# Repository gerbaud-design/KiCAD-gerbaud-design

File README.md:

# KiCAD-gerbaud-design
all the KiCAD files for gerbaud design products and libraries

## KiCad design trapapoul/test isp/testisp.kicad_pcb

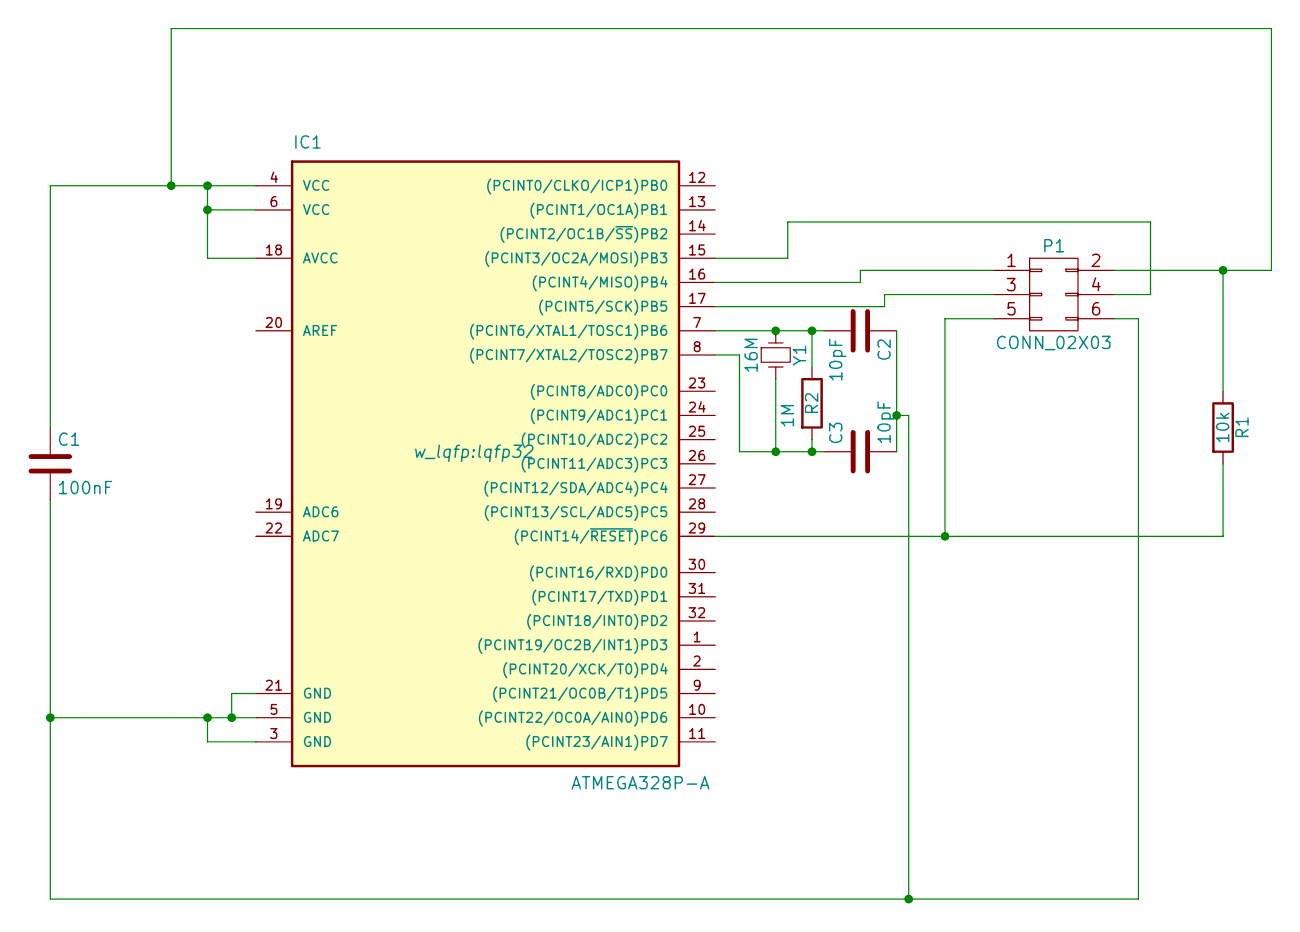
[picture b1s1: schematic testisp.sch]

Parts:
C1: 100nF; C_1206_HandSoldering
C2, C3: 10pF; C_1206_HandSoldering
IC1: ATMEGA328P-A; lqfp32
P1: CONN_02X03; Pin_Header_Straight_2x03_Pitch2.54mm
R1: 10k; R_1206_HandSoldering
R2: 1M; R_1206_HandSoldering
Y1: 16M; Crystal_HC49-SD_SMD

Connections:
unnamed: C1.1, IC1.4 (VCC), IC1.6 (VCC), IC1.18 (AVCC), P1.2, R1.1
unnamed: C1.2, C2.1, C3.2, IC1.3 (GND), IC1.5 (GND), IC1.21 (GND), P1.6
unnamed: C2.2, IC1.7 ((PCINT6/XTAL1/TOSC1)PB6), R2.1, Y1.1
unnamed: C3.1, IC1.8 ((PCINT7/XTAL2/TOSC2)PB7), R2.2, Y1.2
unnamed: IC1.15 ((PCINT3/OC2A/MOSI)PB3), P1.4
unnamed: IC1.16 ((PCINT4/MISO)PB4), P1.1
unnamed: IC1.17 ((PCINT5/SCK)PB5), P1.3
unnamed: IC1.29 ((PCINT14/~RESET~)PC6), P1.5, R1.2

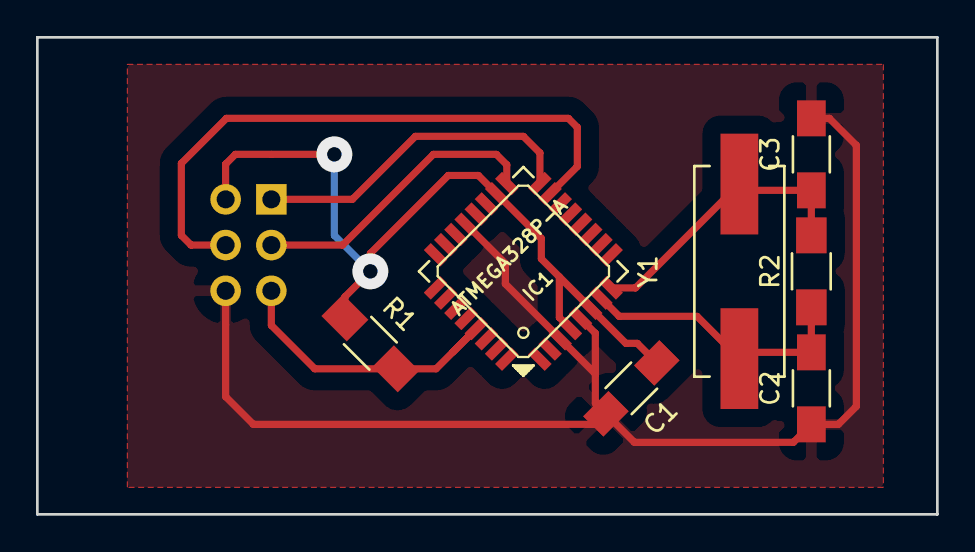
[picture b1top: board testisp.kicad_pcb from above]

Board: 2 copper layers, 50.0 x 26.5 mm, 8 parts (1 on the bottom side), 8 nets.

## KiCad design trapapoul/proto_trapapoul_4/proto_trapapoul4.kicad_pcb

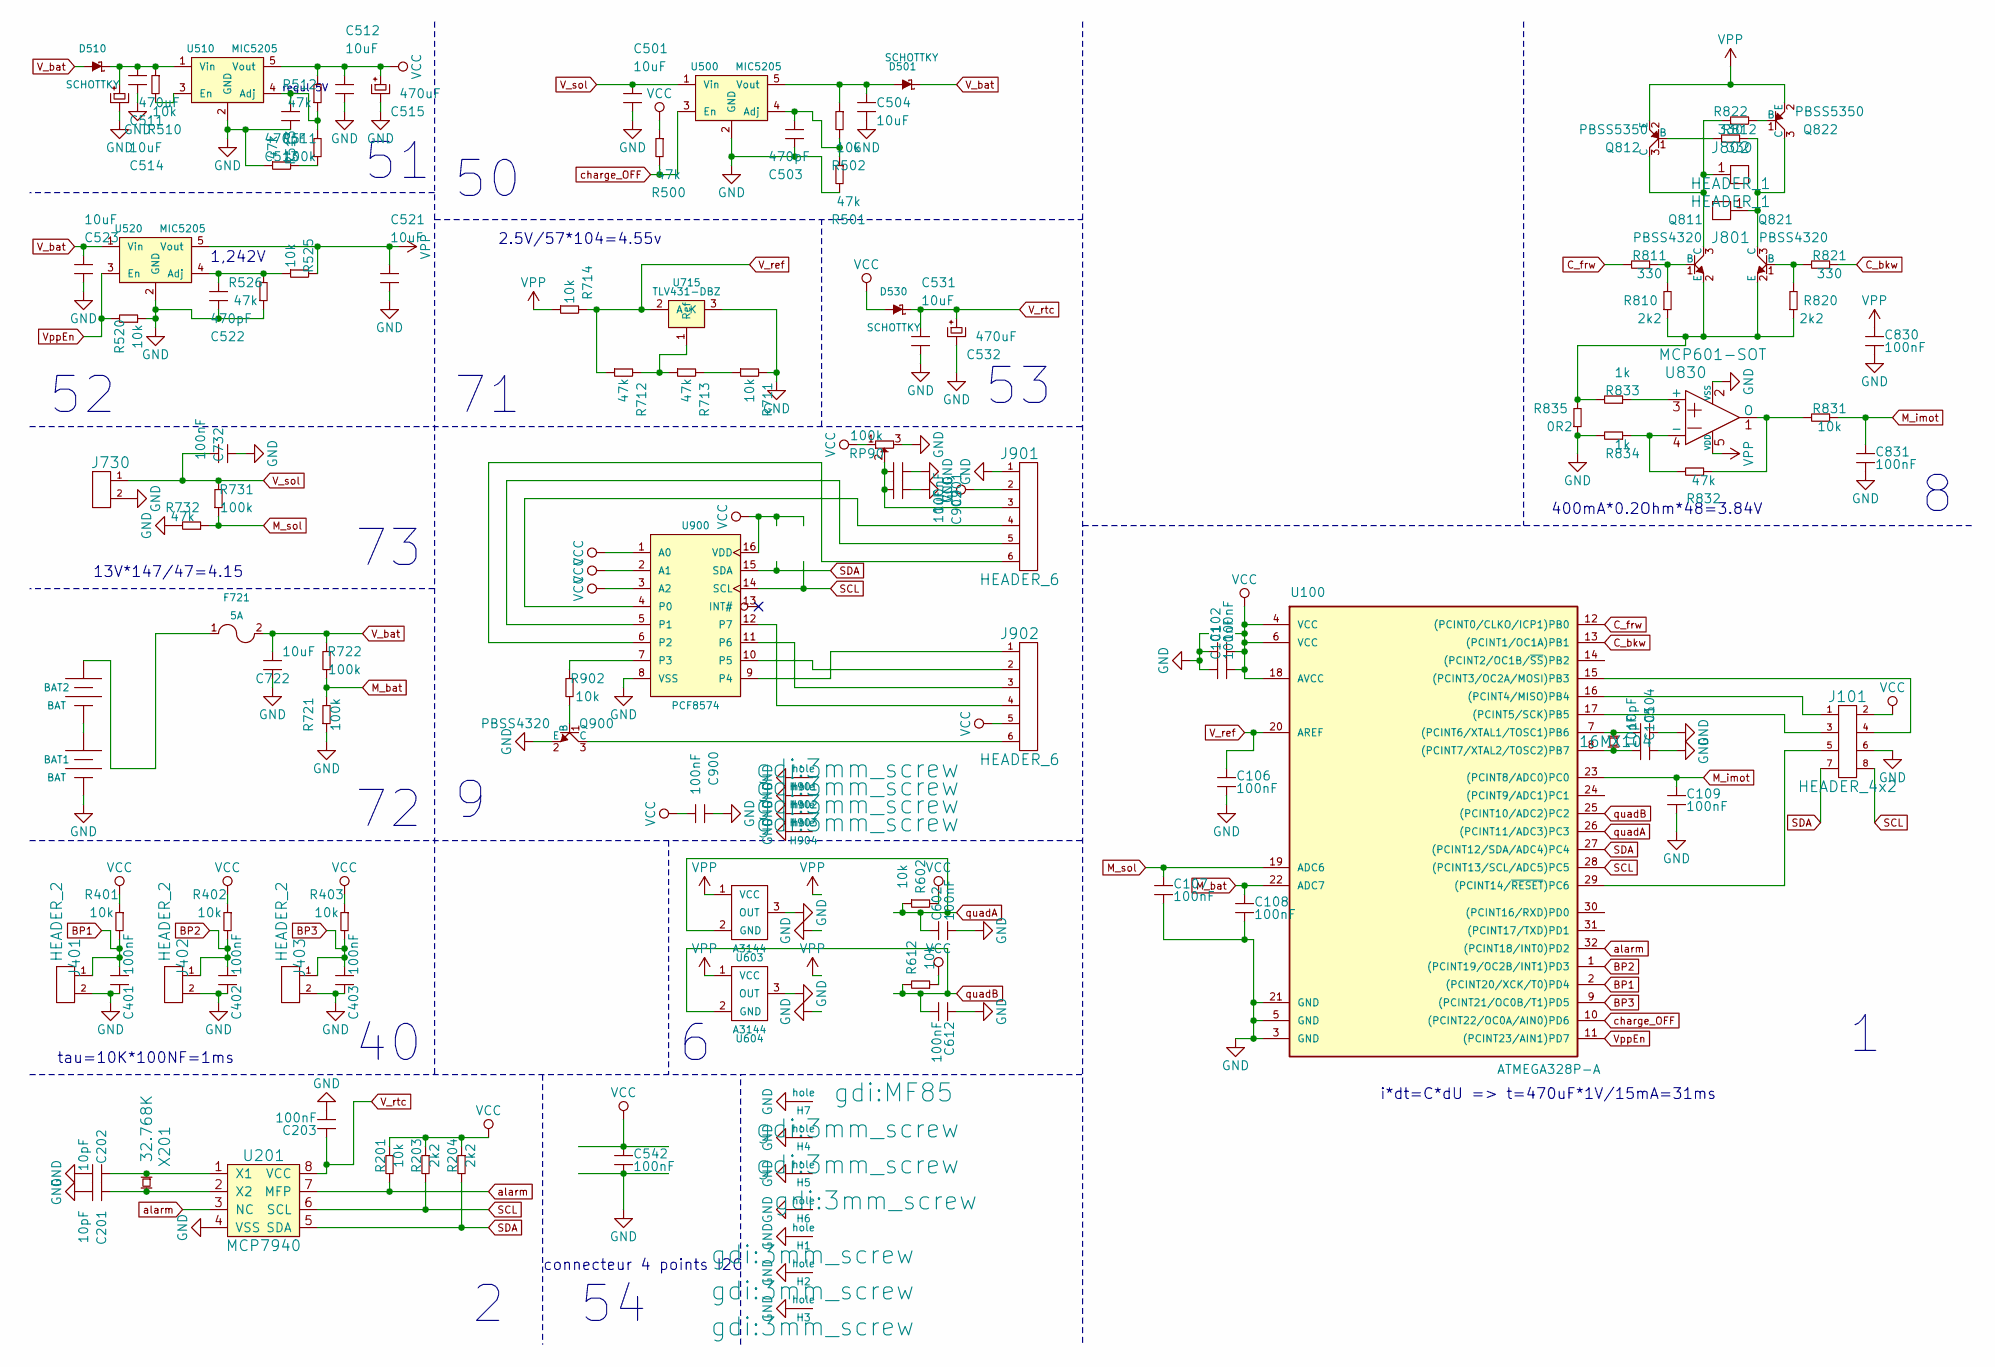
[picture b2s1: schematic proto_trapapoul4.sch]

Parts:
BAT1, BAT2: BAT; HFC1330
C101, C102, C106, C107, C108, C109, C203, C401, C402, C403, C542, C602, C612, C732, C830, C831, C900, C901: 100nF; C_1206
C104, C105, C201, C202: 10pF; C_1206
C501, C504, C512, C514, C521, C523, C531, C722, C902: 10uF; C_1206
C503, C513, C522: 470pF; C_1206
C511, C515, C532: 470uF; C_Radial_D6.3_L11.2_P2.5
D501, D510, D530: SCHOTTKY; SOD-123
F721: 5A; Fuse_SMD1206_Reflow
H1, H2, H3, H4, H5, H6, H901, H902, H903, H904: hole; 3mm_screw
H7: hole; MF85
J101: HEADER_4x2; Pin_Header_Straight_2x04_Pitch2.54mm
J401, J402, J403, J730: HEADER_2; Pin_Header_Straight_1x02
J801, J802: HEADER_1; Pin_Header_Straight_1x01
J901, J902: HEADER_6; Pin_Header_Straight_1x06
Q811, Q821, Q900: PBSS4320; SOT-23
Q812, Q822: PBSS5350; SOT-23
R201, R401, R402, R403, R502, R510, R520, R525, R602, R612, R711, R714, R831, R902: 10k; R_1206
R203, R204, R810, R820: 2k2; R_1206
R500, R501, R512, R513, R526, R712, R713, R732, R832: 47k; R_1206
R511, R721, R722, R731: 100k; R_1206
R811, R812, R821, R822: 330; R_1206
R833, R834: 1k; R_1206
R835: 0R2; R_1206
RP90: 100k; Potentiometer_Triwood_RM-065
U100: ATMEGA328P-A; lqfp32
U201: MCP7940; SOIC-8-N
U500, U510, U520: MIC5205; SOT-23-5
U603, U604: A3144; SOT-23
U715: TLV431-DBZ; SOT-23
U830: MCP601-SOT; SOT-23-5
U900: PCF8574; SO-16-W
X104: 16M; Crystal_HC49-SD_SMD
X201: 32.768K; Crystal_Round_Vertical_3mm_BigPad

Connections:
BP1: C401.1, J401.1, R401.2, U100.2 ((PCINT20/XCK/T0)PD4)
BP2: C402.1, J402.1, R402.2, U100.1 ((PCINT19/OC2B/INT1)PD3)
BP3: C403.1, J403.1, R403.2, U100.9 ((PCINT21/OC0B/T1)PD5)
C_bkw: R821.1, U100.13 ((PCINT1/OC1A)PB1)
C_frw: R811.2, U100.12 ((PCINT0/CLKO/ICP1)PB0)
GND: BAT1.2 (-), C101.1, C102.1, C104.1, C105.1, C106.2, C107.2, C108.2, C109.2, C201.2, C202.2, C203.2, C401.2, C402.2, C403.2, C501.2, C503.2, C504.2, C511.2, C512.2, C513.2, C514.2, C515.2, C521.2, C522.2, C523.2, C531.2, C532.2, C542.2, C602.2, C612.1, C722.2, C732.1, C830.2, C831.2, C900.2, C901.1, C902.1, H1.1, H2.1, H3.1, H4.1, H5.1, H6.1, H7.1, H901.1, H902.1, H903.1, H904.1, J101.6, J401.2, J402.2, J403.2, J730.2, J901.1, Q900.2 (E), R501.2, R513.1, R520.1, R526.1, R711.2, R721.1, R732.2, R834.2, R835.1, RP90.3, U100.3 (GND), U100.5 (GND), U100.21 (GND), U201.4 (VSS), U500.2 (GND), U510.2 (GND), U520.2 (GND), U603.3 (OUT), U604.3 (OUT), U715.3 (K), U830.2 (VSS), U900.8 (VSS)
M_bat: C108.1, R721.2, R722.2, U100.22 (ADC7)
M_imot: C109.1, C831.1, R831.1, U100.23 ((PCINT8/ADC0)PC0)
M_sol: C107.1, R731.1, R732.1, U100.19 (ADC6)
unnamed: BAT1.1 (+), BAT2.2 (-)
unnamed: BAT2.1 (+), F721.1
unnamed: C104.2, U100.7 ((PCINT6/XTAL1/TOSC1)PB6), X104.1
unnamed: C105.2, U100.8 ((PCINT7/XTAL2/TOSC2)PB7), X104.2
unnamed: C201.1, U201.2 (X2), X201.2
unnamed: C202.1, U201.1 (X1), X201.1
unnamed: C503.1, R501.1, R502.2, U500.4 (Adj)
unnamed: C504.1, D501.2 (A), R502.1, U500.5 (Vout)
unnamed: C511.1, C514.1, D510.1 (K), R510.1, U510.1 (Vin)
unnamed: C513.1, R511.2, R512.1, U510.4 (Adj)
unnamed: C522.1, R525.1, R526.2, U520.4 (Adj)
unnamed: C901.2, C902.2, J901.3, RP90.2
unnamed: J101.1, U100.16 ((PCINT4/MISO)PB4)
unnamed: J101.3, U100.17 ((PCINT5/SCK)PB5)
unnamed: J101.4, U100.15 ((PCINT3/OC2A/MOSI)PB3)
unnamed: J101.5, U100.29 ((PCINT14/~RESET~)PC6)
unnamed: J801.1, Q821.3 (C), Q822.3 (C), R812.1
unnamed: J802.1, Q811.3 (C), Q812.3 (C), R822.1
unnamed: J901.4, U900.4 (P0)
unnamed: J901.5, U900.5 (P1)
unnamed: J901.6, U900.6 (P2)
unnamed: J902.1, U900.9 (P4)
unnamed: J902.2, U900.10 (P5)
unnamed: J902.3, U900.11 (P6)
unnamed: J902.4, U900.12 (P7)
unnamed: J902.6, Q900.3 (C)
unnamed: Q811.1 (B), R810.2, R811.1
unnamed: Q811.2 (E), Q821.2 (E), R810.1, R820.1, R833.2, R835.2
unnamed: Q812.1 (B), R812.2
unnamed: Q821.1 (B), R820.2, R821.2
unnamed: Q822.1 (B), R822.2
unnamed: Q900.1 (B), R902.2
unnamed: R510.2, U510.3 (En)
unnamed: R511.1, R513.2
unnamed: R711.1, R713.2
unnamed: R712.2, R713.1, U715.1 (Ref)
unnamed: R831.2, R832.1, U830.1 (O)
unnamed: R832.2, R834.1, U830.4 (-)
unnamed: R833.1, U830.3 (+)
unnamed: R902.1, U900.7 (P3)
SCL: J101.8, R203.2, U100.28 ((PCINT13/SCL/ADC5)PC5), U201.6 (SCL), U900.14 (SCL)
SDA: J101.7, R204.2, U100.27 ((PCINT12/SDA/ADC4)PC4), U201.5 (SDA), U900.15 (SDA)
VCC: C101.2, C102.2, C512.1, C515.1, C542.1, C900.1, D530.2 (A), J101.2, J901.2, J902.5, R201.1, R203.1, R204.1, R401.1, R402.1, R403.1, R500.1, R512.2, R602.2, R612.1, RP90.1, U100.4 (VCC), U100.6 (VCC), U100.18 (AVCC), U510.5 (Vout), U900.1 (A0), U900.2 (A1), U900.3 (A2), U900.16 (VDD)
VPP: C521.1, C830.1, Q812.2 (E), Q822.2 (E), R525.2, R714.1, U520.5 (Vout), U603.1 (VCC), U604.1 (VCC), U830.5 (VDD)
V_bat: C523.1, C722.1, D501.1 (K), D510.2 (A), F721.2, R722.1, U520.1 (Vin)
V_ref: C106.1, R712.1, R714.2, U100.20 (AREF), U715.2 (A)
V_rtc: C203.1, C531.1, C532.1, D530.1 (K), U201.8 (VCC)
V_sol: C501.1, C732.2, J730.1, R731.2, U500.1 (Vin)
VppEn: R520.2, U100.11 ((PCINT23/AIN1)PD7), U520.3 (En)
alarm: R201.2, U100.32 ((PCINT18/INT0)PD2), U201.3 (NC), U201.7 (MFP)
charge_OFF: R500.2, U100.10 ((PCINT22/OC0A/AIN0)PD6), U500.3 (En)
quadA: C602.1, R602.1, U100.26 ((PCINT11/ADC3)PC3), U603.2 (GND)
quadB: C612.2, R612.2, U100.25 ((PCINT10/ADC2)PC2), U604.2 (GND)

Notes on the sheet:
regul 5V
connecteur 4 points I2C
1,242V
2.5V/57*104=4.55v
tau=10K*100NF=1ms
13V*147/47=4.15
400mA*0.2Ohm*48=3.84V
i*dt=C*dU => t=470uF*1V/15mA=31ms

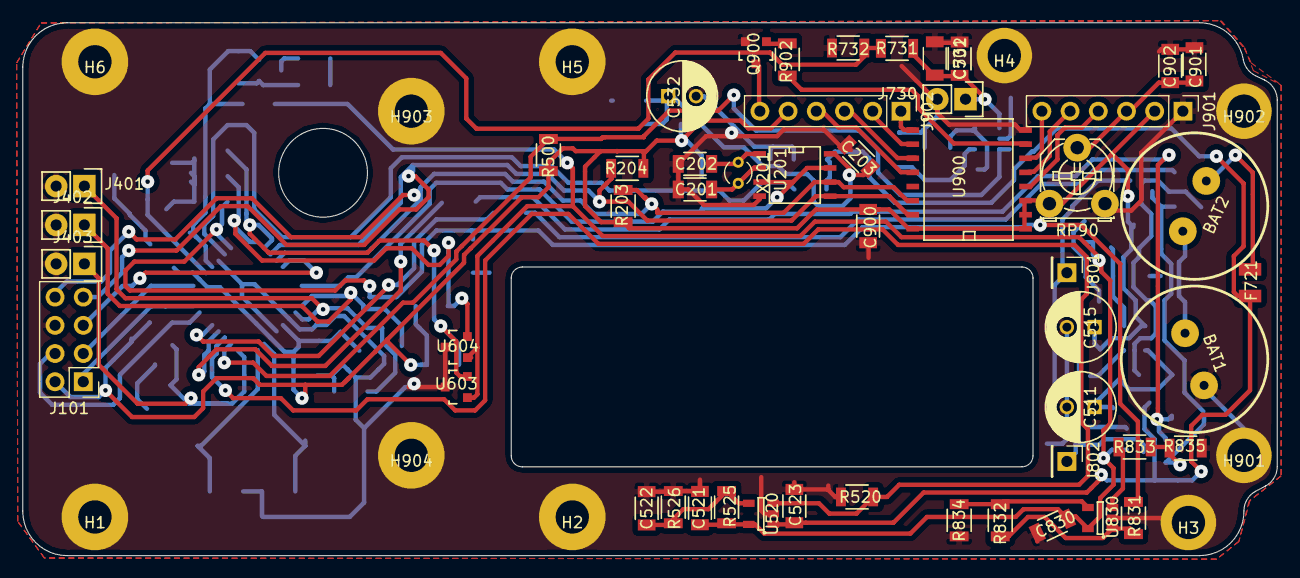
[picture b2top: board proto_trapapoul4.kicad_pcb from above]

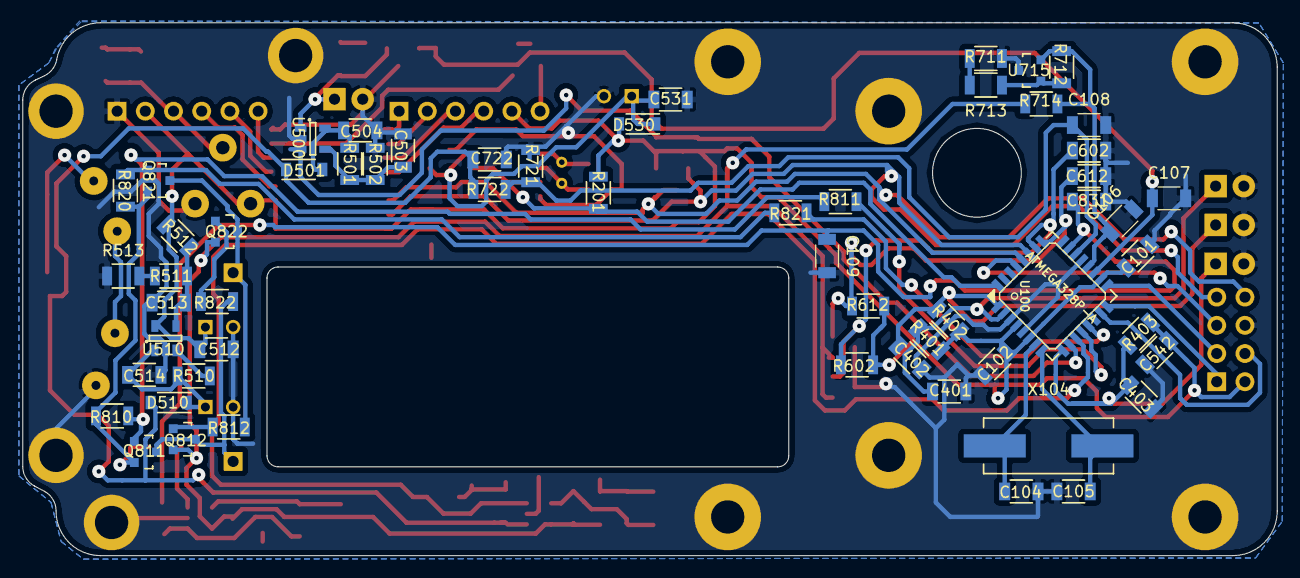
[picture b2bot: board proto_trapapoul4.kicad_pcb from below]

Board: 2 copper layers, 113.0 x 48.0 mm, 118 parts (58 on the bottom side), 62 nets.

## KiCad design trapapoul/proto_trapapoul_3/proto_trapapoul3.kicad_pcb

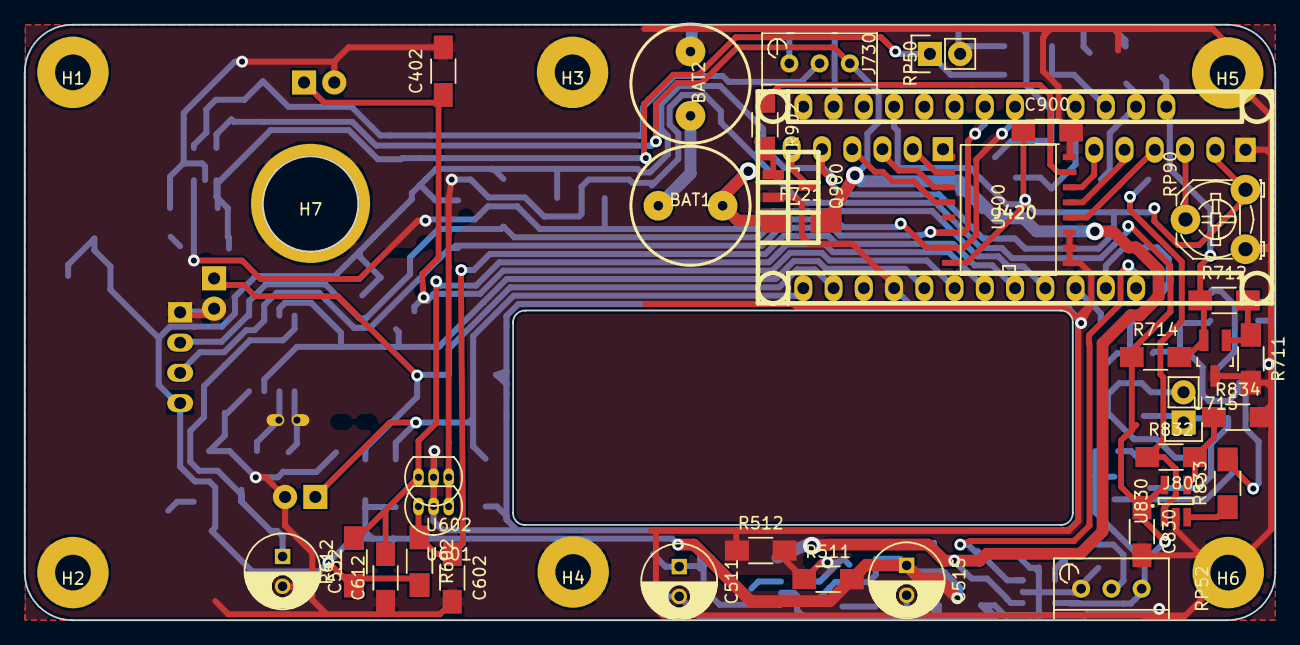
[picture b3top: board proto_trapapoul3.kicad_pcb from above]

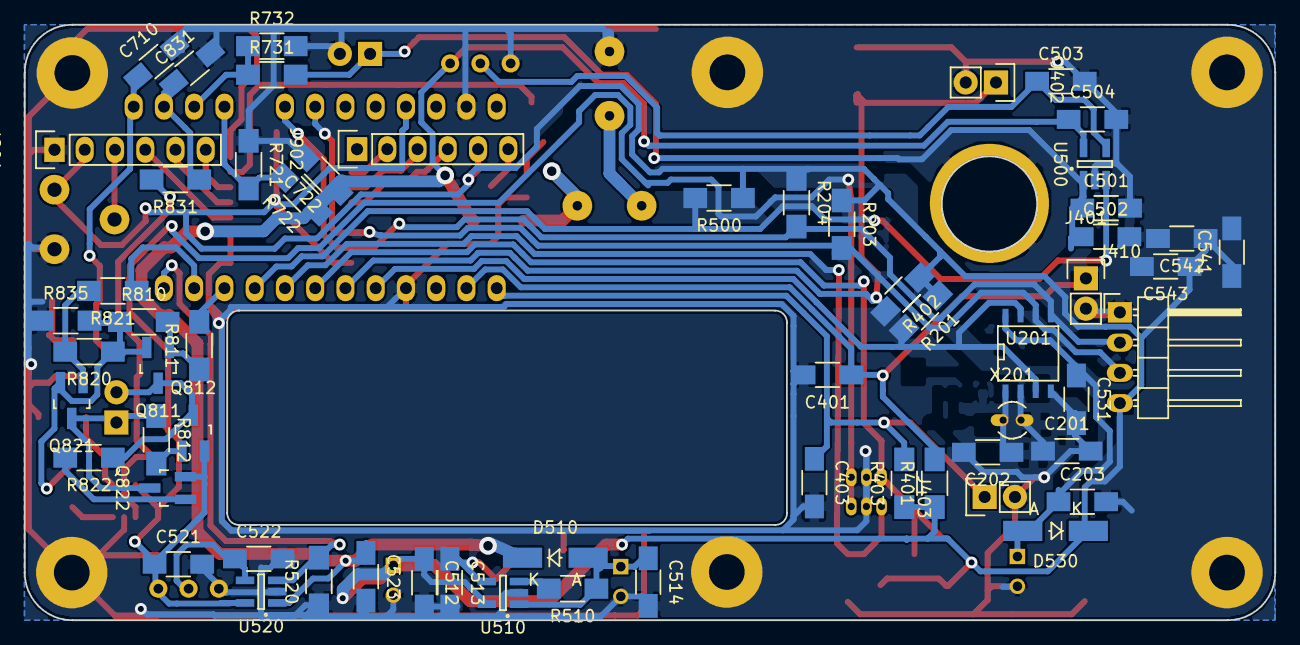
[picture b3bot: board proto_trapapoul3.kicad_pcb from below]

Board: 2 copper layers, 105.0 x 50.0 mm, 101 parts (60 on the bottom side), 53 nets.

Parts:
BAT1, BAT2: BAT; HFC1025
C201, C202: 10p; C_1206_HandSoldering
C203, C401, C402, C403, C502, C541, C710: 10n; C_1206_HandSoldering
C501, C504, C512, C514, C521, C523, C531, C543, C722: 10uF; C_1206_HandSoldering
C503, C513, C522: 470p; C_1206_HandSoldering
C511, C515, C532: 470uF; C_Radial_D6.3_L11.2_P2.5
C542, C602, C612, C900: 100nF; C_1206_HandSoldering
C830, C831: 100n; C_1206_HandSoldering
D510, D530: SCHOTTKY; MiniMELF_Handsoldering
F721: 5A; Fuse_SMD1206_HandSoldering
H1, H2, H3, H4, H5, H6: hole; 3mm_screw
H7: hole; MF85
J401, J402, J403, J730, J800: HEADER_2; Pin_Header_Straight_1x02
J410: HEADER_4; Pin_Header_Angled_1x04
J420: Arduino_Nano_Header; arduino_nano_header
J901, J902: HEADER_6; Pin_Header_Straight_1x06
Q811, Q821, Q900: PBSS4320; SOT-23_Handsoldering
Q812, Q822: PBSS5350; SOT-23_Handsoldering
R201, R401, R402, R403, R500, R510, R511, R520, R711, R714, R722, R731, R832: 10k; R_1206_HandSoldering
R203, R204, R732: 2.2k; R_1206_HandSoldering
R512, R810, R820: 3k3; R_1206_HandSoldering
R602, R612: 4k7; R_1206_HandSoldering
R712, R721, R902: 4.7k; R_1206_HandSoldering
R811, R812, R821, R822: 330; R_1206_HandSoldering
R831, R833, R834: 1k; R_1206_HandSoldering
R835: 0R2; R_1206_HandSoldering
RP50, RP52: 10k; Potentiometer_Bourns_3296W_3-8Zoll_Inline_ScrewUp
RP90: 10k; Potentiometer_Triwood_RM-065
U201: MCP7940; SOIC-8-N
U500, U510, U520: MIC5205; SOT-23-5_Handsoldering
U601, U602: A3144; TO-92_Inline_Narrow_Oval
U715: TLV431-DBZ; SOT-23_Handsoldering
U830: MCP601-SOT; SOT-23-5_Handsoldering
U900: PCF8574; SO-16-W
X201: 32.768K; Crystal_Round_Vertical_3mm_BigPad

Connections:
BP1: C401.1, J401.1, J420.2, R401.2
BP2: C402.1, J402.1, J420.6, R402.2
BP3: C403.1, J403.1, J420.1, R403.2
C_bkw: J420.11, R821.1
C_frw: J420.10, R811.2
GND: BAT2.2, C201.2, C202.2, C203.2, C401.2, C402.2, C403.2, C501.2, C502.2, C503.2, C504.2, C511.2, C512.2, C513.2, C514.2, C515.2, C521.2, C522.2, C523.2, C531.2, C532.2, C541.2, C542.2, C543.2, C602.2, C612.1, C710.2, C722.2, C830.2, C831.2, C900.2, H1.1, H2.1, H3.1, H4.1, H5.1, H6.1, H7.1, J401.2, J402.2, J403.2, J410.1, J420.4, J420.29, J730.2, J901.1, Q900.2, R512.1, R520.1, R711.2, R721.1, R732.2, R834.2, R835.1, RP50.1, RP52.1, RP90.1, U201.4, U500.2, U510.2, U520.2, U601.2, U602.2, U715.3, U830.2, U900.1, U900.2, U900.3, U900.8
M_bat: J420.21, R721.2, R722.2
M_imot: C831.1, J420.19, R831.1
M_sol: J420.20, R731.1, R732.1
unnamed: BAT1.1, F721.1
unnamed: BAT1.2, BAT2.1
unnamed: C201.1, U201.2, X201.2
unnamed: C202.1, U201.1, X201.1
unnamed: C503.1, RP50.2, U500.4
unnamed: C511.1, C514.1, D510.2, R510.1, U510.1
unnamed: C513.1, R511.1, R512.2, U510.4
unnamed: C522.1, RP52.2, U520.4
unnamed: J901.3, RP90.2
unnamed: J901.4, U900.4
unnamed: J901.5, U900.5
unnamed: J901.6, U900.6
unnamed: J902.1, U900.9
unnamed: J902.2, U900.10
unnamed: J902.3, U900.11
unnamed: J902.4, U900.12
unnamed: J902.6, Q900.3
unnamed: Q811.1, R810.2, R811.1
unnamed: Q811.2, Q821.2, R810.1, R820.1, R833.2, R835.2
unnamed: Q812.1, R812.2
unnamed: Q821.1, R820.2, R821.2
unnamed: Q822.1, R822.2
unnamed: Q900.1, R902.2
unnamed: R510.2, U510.3
unnamed: R711.1, R712.2, U715.1
unnamed: R831.2, R832.1, U830.1
unnamed: R832.2, R834.1, U830.4
unnamed: R833.1, U830.3
unnamed: R902.1, U900.7
SCL: J410.3, J420.24, R203.2, U201.6, U900.14
SDA: J410.2, J420.23, R204.2, U201.5, U900.15
VCC: C512.1, C515.1, C541.1, C542.1, C543.1, C900.1, D530.1, J410.4, J420.27, J901.2, J902.5, R201.1, R203.1, R204.1, R401.1, R402.1, R403.1, R500.1, R511.2, R602.2, R612.1, RP90.3, U510.5, U900.16
VPP: C521.1, C830.1, Q812.2, Q822.2, R714.1, RP52.3, U520.5, U601.1, U602.1, U830.5
V_bat: C504.1, C523.1, C722.1, D510.1, F721.2, R722.1, RP50.3, U500.5, U520.1
V_ref: C710.1, J420.18, R712.1, R714.2, U715.2
V_rtc: C203.1, C531.1, C532.1, D530.2, U201.8
V_sol: C501.1, C502.1, J730.1, R731.2, U500.1
VppEn: J420.12, R520.2, U520.3
alarm: J420.5, R201.2, U201.3, U201.7
charge_OFF: J420.9, R500.2, U500.3
mot_A: J800.1, Q821.3, Q822.3, R812.1
mot_B: J800.2, Q811.3, Q812.3, R822.1
quadA: C602.1, J420.8, R602.1, U601.3
quadB: C612.2, J420.7, R612.2, U602.3

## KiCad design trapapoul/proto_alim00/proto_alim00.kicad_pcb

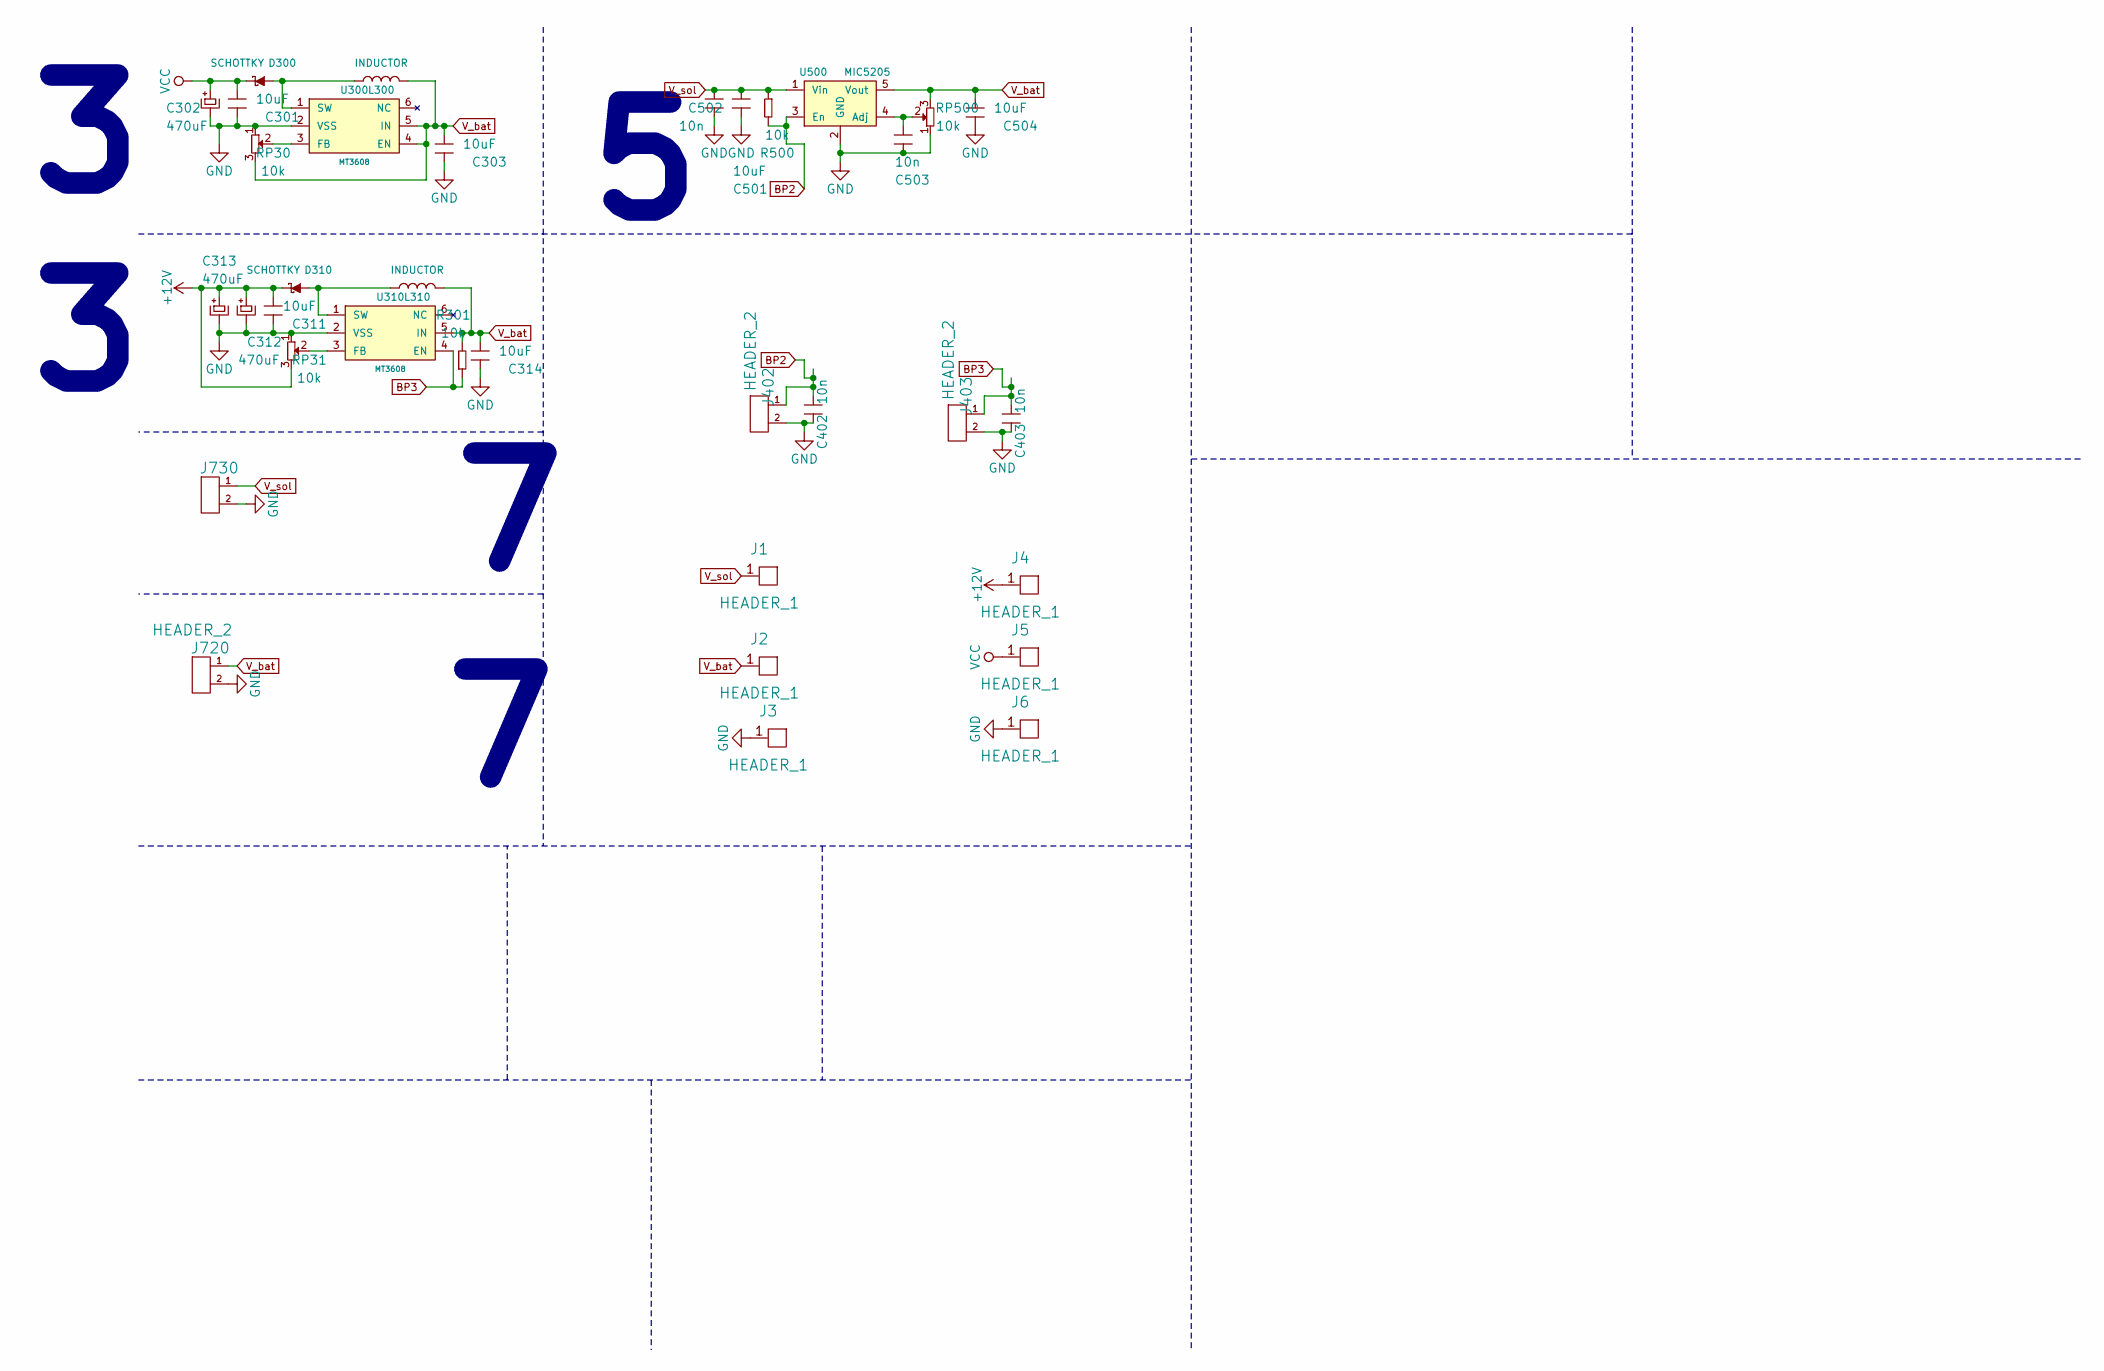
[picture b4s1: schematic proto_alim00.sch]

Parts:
C301, C303, C311, C314, C501, C504: 10uF; C_1206_HandSoldering
C302, C312, C313: 470uF; C_Radial_D8_L11.5_P3.5
C402, C403, C502, C503: 10n; C_1206_HandSoldering
D300, D310: SCHOTTKY; MiniMELF_Handsoldering
J1, J2, J3, J4, J5, J6: HEADER_1; Pin_Header_Straight_1x01
J402, J403, J720, J730: HEADER_2; Pin_Header_Straight_1x02
L300, L310: INDUCTOR; R_1206_HandSoldering
R301, R500: 10k; R_1206_HandSoldering
RP30, RP31, RP500: 10k; Potentiometer_Triwood_RM-065
U300, U310: MT3608; SOT-23-6_Handsoldering
U500: MIC5205; SOT-23-5_Handsoldering

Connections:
+12V: C311.1, C312.1, C313.1, D310.2 (K), J4.1, RP31.3
BP2: C402.1, J402.1, R500.2, U500.3 (En)
BP3: C403.1, J403.1, R301.1, U310.4 (EN)
GND: C301.2, C302.2, C303.2, C311.2, C312.2, C313.2, C314.2, C402.2, C403.2, C501.2, C502.2, C503.2, C504.2, J3.1, J6.1, J402.2, J403.2, J720.2, J730.2, RP30.1, RP31.1, RP500.1, U300.2 (VSS), U310.2 (VSS), U500.2 (GND)
unnamed: C503.1, RP500.2, U500.4 (Adj)
unnamed: D300.1 (A), L300.1, U300.1 (SW)
unnamed: D310.1 (A), L310.1, U310.1 (SW)
unnamed: RP30.2, U300.3 (FB)
unnamed: RP31.2, U310.3 (FB)
VCC: C301.1, C302.1, D300.2 (K), J5.1
V_bat: C303.1, C314.1, C504.1, J2.1, J720.1, L300.2, L310.2, R301.2, RP30.3, RP500.3, U300.4 (EN), U300.5 (IN), U310.5 (IN), U500.5 (Vout)
V_sol: C501.1, C502.1, J1.1, J730.1, R500.1, U500.1 (Vin)

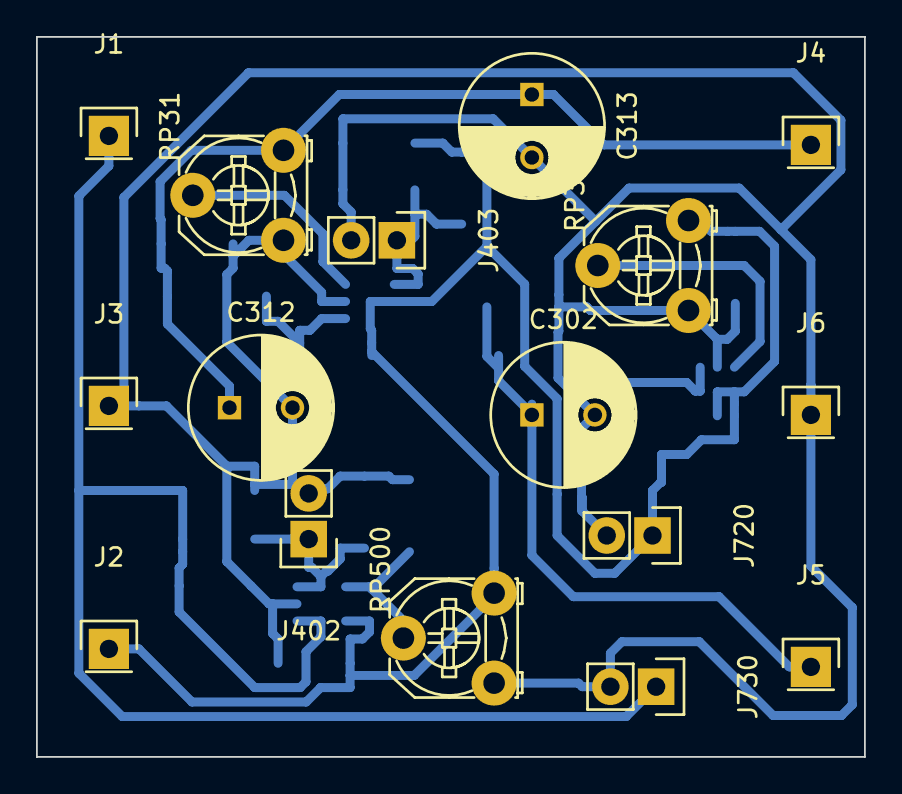
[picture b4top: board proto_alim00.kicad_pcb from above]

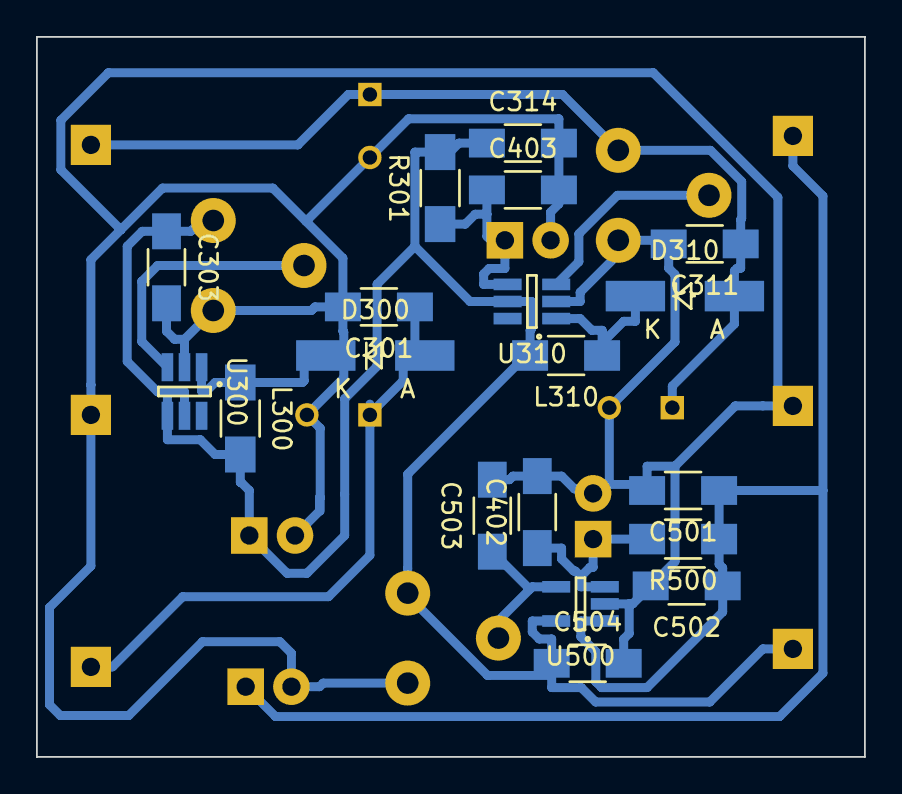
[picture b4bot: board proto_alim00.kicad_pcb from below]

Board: 2 copper layers, 46.0 x 40.0 mm, 35 parts (19 on the bottom side), 12 nets.
